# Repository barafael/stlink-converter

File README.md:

# stlink-converter

The little arrows ('∨') mark the side of the stlink socket with the gap.

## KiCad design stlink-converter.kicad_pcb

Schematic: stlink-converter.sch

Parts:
H1, H2: MountingHole; MountingHole_3mm
J1: Conn_02x07_Odd_Even; PinHeader_2x07_P1.27mm_Vertical
J2: Conn_01x06; PinHeader_1x06_P2.54mm_Vertical
J3: Conn_02x10_Odd_Even; PinHeader_2x10_P2.54mm_Vertical
SW1: SW_Push; SW_Push_1P1T_NO_CK_KSC7xxJ

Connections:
GND: J1.5, J1.7, J2.3, J3.4, J3.6, J3.8, J3.10, J3.12, J3.14, J3.16, J3.18, J3.20, SW1.2
GNDDETECT: J1.11, J2.6
T_JCLK: J1.6, J3.9
T_JRCLK: J1.9, J3.11
T_JTDI: J1.10, J3.5
T_JTDO: J1.8, J3.13
T_JTMS: J1.4, J3.7
T_NRST: J1.12, J3.15, SW1.1
T_SUPPLY: J2.1, J3.19
T_VCC: J1.3, J2.2, J3.1
T_VCP_RX: J1.13, J2.5
T_VCP_TX: J1.14, J2.4

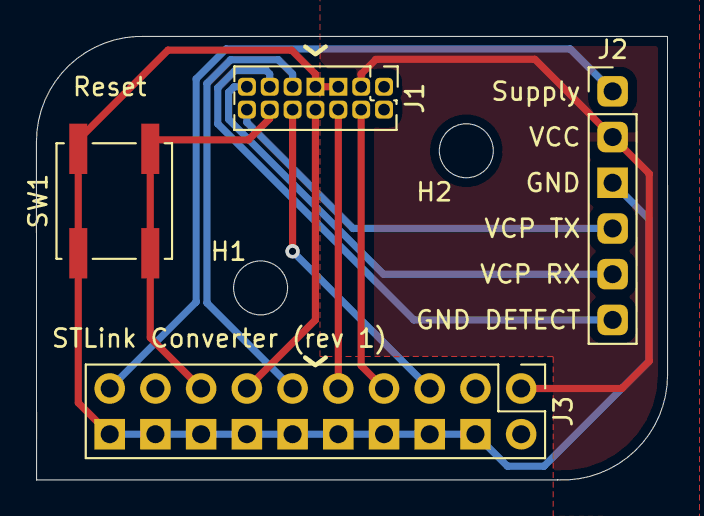
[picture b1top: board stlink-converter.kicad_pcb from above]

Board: 2 copper layers, 35.1 x 24.6 mm, 6 parts (0 on the bottom side), 12 nets.

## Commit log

2021-02-09 Rename files
2021-11-17 Fix button footprint
2021-11-17 Fix typo VCC_RX->VCP_RX
2023-05-29 Update design files for kicad 7
    also adds another pin header for getting at the most important pins
